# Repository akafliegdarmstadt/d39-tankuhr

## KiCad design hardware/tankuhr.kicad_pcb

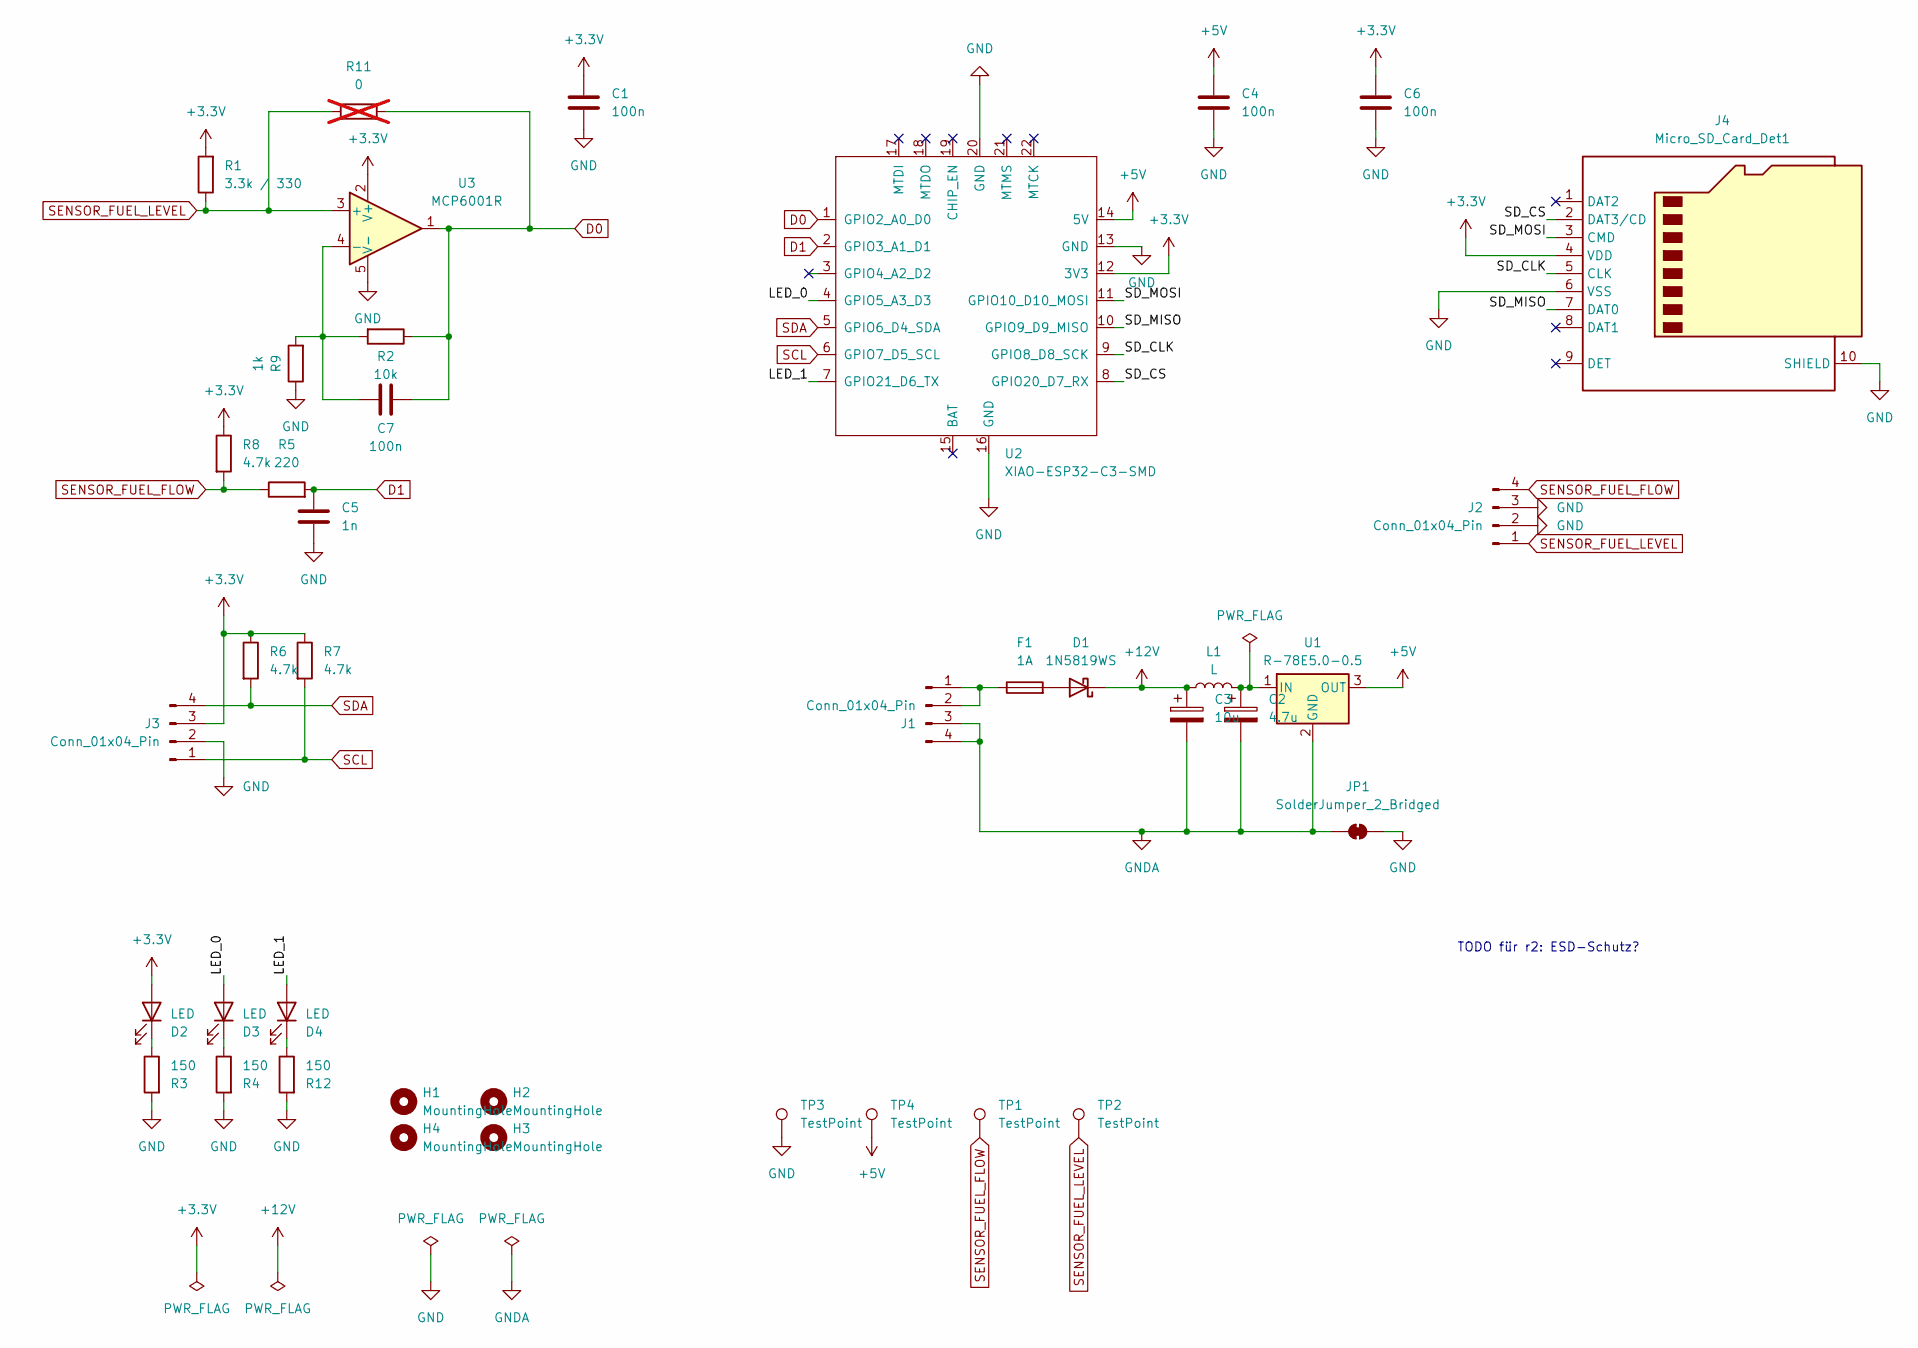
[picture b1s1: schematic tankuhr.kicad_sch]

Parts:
C1, C4, C6, C7: 100n; C_0805_2012Metric_Pad1.18x1.45mm_HandSolder
C2: 4.7u; CP_Radial_D5.0mm_P2.00mm
C3: 10u; CP_Radial_D5.0mm_P2.00mm
C5: 1n; C_0805_2012Metric_Pad1.18x1.45mm_HandSolder
D1: 1N5819WS; D_SOD-323
D2, D3, D4: LED; LED_0805_2012Metric_Pad1.15x1.40mm_HandSolder
F1: 1A; Fuse_1206_3216Metric
H1, H2, H3, H4: MountingHole; MountingHole_3.2mm_M3
J1, J2, J3: Conn_01x04_Pin; Molex_PicoBlade_53398-0471_1x04-1MP_P1.25mm_Vertical
J4: Micro_SD_Card_Det1; microSD_HC_Molex_104031-0811
JP1: SolderJumper_2_Bridged; SolderJumper-2_P1.3mm_Bridged2Bar_Pad1.0x1.5mm
L1: L; RECOM RLS-120
R1: 3.3k / 330; R_0805_2012Metric_Pad1.20x1.40mm_HandSolder
R2: 10k; R_0805_2012Metric_Pad1.20x1.40mm_HandSolder
R3, R4, R12: 150; R_0805_2012Metric_Pad1.20x1.40mm_HandSolder
R5: 220; R_0805_2012Metric_Pad1.20x1.40mm_HandSolder
R6, R7, R8: 4.7k; R_0805_2012Metric_Pad1.20x1.40mm_HandSolder
R9: 1k; R_0805_2012Metric_Pad1.20x1.40mm_HandSolder
R11: 0; R_0805_2012Metric_Pad1.20x1.40mm_HandSolder; not fitted
TP1, TP2, TP3, TP4: TestPoint; TestPoint_Pad_D1.0mm
U1: R-78E5.0-0.5; Converter_DCDC_RECOM_R-78E-0.5_THT
U2: XIAO-ESP32-C3-SMD; XIAO-ESP32C3-SMD
U3: MCP6001R; SOT-23-5

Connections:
+3.3V: C1.1, C6.1, D2.2 (A), J3.3, J4.4 (VDD), R1.2, R6.1, R7.1, R8.1, U2.12 (3V3), U3.2 (V+)
+5V: C4.1, TP4.1, U1.3 (OUT), U2.14 (5V)
+12V: C3.1, D1.1 (K), L1.1
/LED_0: D3.2 (A), U2.4 (GPIO5_A3_D3)
/LED_1: D4.2 (A), U2.7 (GPIO21_D6_TX)
/SD_CLK: J4.5 (CLK), U2.9 (GPIO8_D8_SCK)
/SD_CS: J4.2 (DAT3/CD), U2.8 (GPIO20_D7_RX)
/SD_MISO: J4.7 (DAT0), U2.10 (GPIO9_D9_MISO)
/SD_MOSI: J4.3 (CMD), U2.11 (GPIO10_D10_MOSI)
D0: C7.2, R2.1, R11.2, U2.1 (GPIO2_A0_D0), U3.1
D1: C5.1, R5.2, U2.2 (GPIO3_A1_D1)
GND: C1.2, C4.2, C5.2, C6.2, J2.2, J2.3, J3.2, J4.6 (VSS), J4.10 (SHIELD), JP1.2 (B), R3.2, R4.2, R9.1, R12.2, TP3.1, U2.13 (GND), U2.16 (GND), U2.20 (GND), U3.5 (V-)
GNDA: C2.2, C3.2, J1.3, J1.4, JP1.1 (A), U1.2 (GND)
unnamed: D1.2 (A), F1.2
unnamed: D2.1 (K), R3.1
unnamed: D3.1 (K), R4.1
unnamed: D4.1 (K), R12.1
unnamed: F1.1, J1.1, J1.2
unnamed: C2.1, L1.2, U1.1 (IN)
unnamed: C7.1, R2.2, R9.2, U3.4 (-)
SCL: J3.1, R7.2, U2.6 (GPIO7_D5_SCL)
SDA: J3.4, R6.2, U2.5 (GPIO6_D4_SDA)
SENSOR_FUEL_FLOW: J2.4, R5.1, R8.2, TP1.1
SENSOR_FUEL_LEVEL: J2.1, R1.1, R11.1, TP2.1, U3.3 (+)

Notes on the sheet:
TODO für r2: ESD-Schutz?

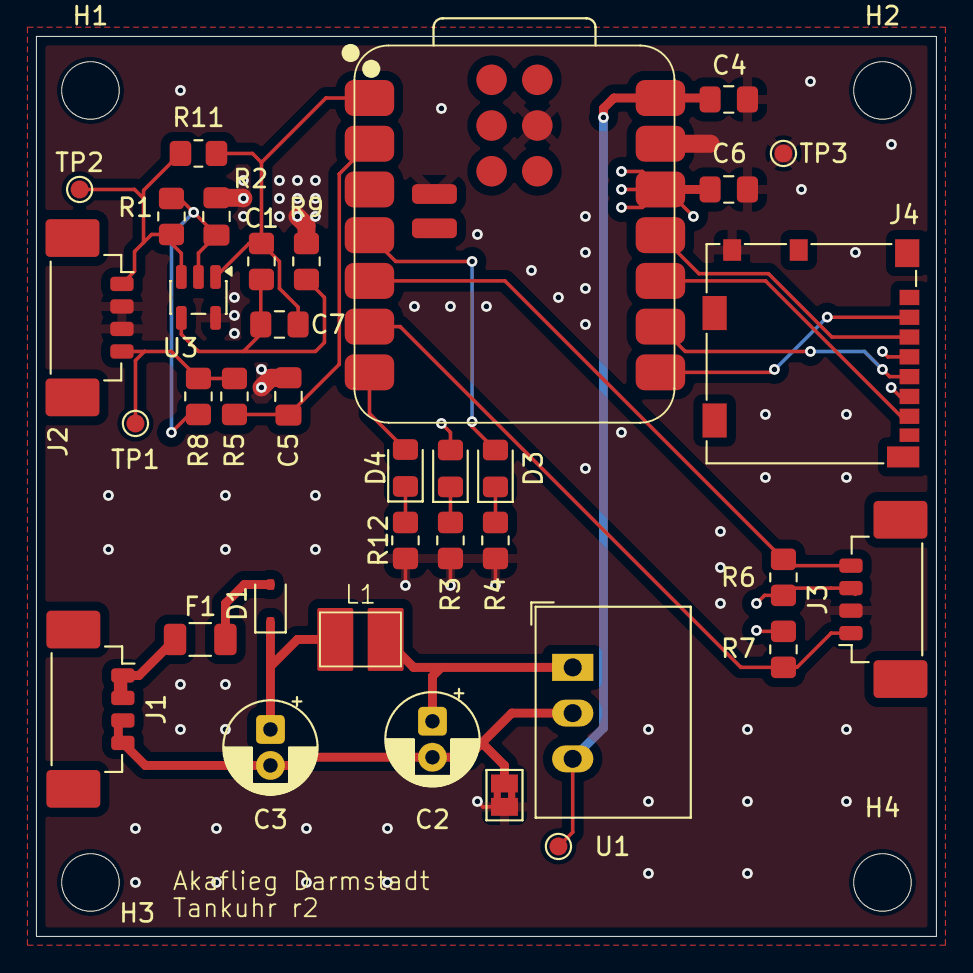
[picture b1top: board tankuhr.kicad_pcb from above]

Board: 4 copper layers, 50.0 x 50.0 mm, 40 parts (0 on the bottom side), 24 nets.

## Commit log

2025-11-14 start with r2 hardware
2025-11-14 add r1 BOM
2025-11-14 add filter simulation
2025-11-15 adaptive process noise estimation
2025-11-20 add first software revision
2025-11-20 add software/README.md
2025-11-20 fix the first bugs
2025-11-23 complete r2 hardware
2025-11-25 hardware: new filter design
2025-11-25 hardware: start BOM in kicad
2025-11-26 hardware: fix clearing violations
2025-11-26 add LCSC BOM
2025-12-03 test
